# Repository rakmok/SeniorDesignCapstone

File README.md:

# SeniorDesignCapstone

This is the repository to record and motivate our capstone project for ECE 445: Senior Design in the Spring of 2025 titled PawFeast: Food on Demand. The group members are Arash Amiri, Kathryn Thompson, and Omkar Kulkarni.

The project entails the analysis, design, and build of a pet food dispensory system. If you wish to see each member's notebook, you can switch branches in github.com by clicking main or run git checkout \[member_first_name]-notebook. Each member hosts their own notebook on a different branch. The Hardware folder contains all of our KiCAD boards and other libraries. The images folder is only meant for displaying images to the README and the Assignments folder includes all of our important documents.

# Problem

All household pet owners must remember to feed their pets—whether they are birds, guinea pigs, rabbits, dogs, or cats—at set periods during the day. But there can be times when people forget to feed their pets, double feed them, or have trouble feeding them on schedule. This can be due to poor communication between family members or even occur when pet owners come home late from work or prior commitments. During these times, pets either overeat, go hungry, or eat irregularly. As a result, timer-based pet feeders have been developed to release food at set intervals. When food sits out for extended periods of time, the risk of the food becoming stale or getting infected with bugs increases drastically.

If an insect is near your food, it is a common reaction to remove or swat it away, but that mechanism is not present for the pet’s food bowl, especially when the family is not at home. Another issue is that smarter pets can nose into the food storage and overeat or eat something that their bodies will reject (like chocolate for dogs). With a set schedule to limit food dispensation throughout the day, the pet will not take advantage of either a careless overpour of food or of an unmanned food station. Furthermore, data on how much food was dispensed and eaten will help track and optimize the pet’s eating habits.

# Solution

We are seeking to solve this problem by having timers coupled with a button and RFID component to release food—thus preventing overeating. Given all of these conditions, the dispenser will release the pet food. This ensures that the pet is not only fed on time, but that the food is not polluted when the pet goes to eat; additionally, a chime will go off signaling to the pet that it is time for them to eat. We will incorporate a notification system to alert the owner(s) whether the pet has eaten or when the food store has low levels of food.

If the pet were to not eat all the food at once and leave the food dispenser, the pressure sensor will tell the dispenser to cover the food until the pet returns ensuring freshness and preventing bugs.

# Solution Components

## Subsystem 1: Refilling Food Store

The subsystem for checking if the food store is empty will include a through-beam optical sensor that is able to determine whether an object is present—this will serve to detect whether the food inside of the container is low and needs to be refilled. When the food store reaches a certain level, a signal will be sent to subsystem 6 (the brain), which will send an automated message to notify the owner to refill the food store.

## Subsystem 2: Power System

The power system will supply energy to all of the various subsystems, including the microcontroller of subsystem 6 (the brain), the stepper motor driver in subsystem 3, and the various sensors in subsystems 1 (refilling food) and 3 (food dispenser). The low voltage buses will be 3.3V, 12V, and 5V, all of which will be powered by a combination of rechargeable lithium-ion batteries with voltage regulators and buck converters. This compact, custom 3s2p battery pack will allow the pet dispenser to be portable, even for family vacations or road trips—more importantly, it will provide a steady current, even when the pack voltage drops (unlike standard AA/AAA cells). The 12V to 3.3V regulator chip will be Monolithic Power Systems’s MP2315SGJ-Z, which can take a 12V input and output up to 2.5A [4.7]. The 12V to 5V regulator chip will be Monolithic Power Systems’s MP2338GTL-Z [4.6]. The 12V input into the motor driver IC circuit will come straight from the battery pack. There will also be a backup supply voltage of 5V from a typical barrel jack wall-outlet, integrated into the brain board. This will implement the AMS1117 LDO, which is perfect for 5V to 3.3V power conversion. Just to be clear, this 5V barrel-jack addition will just be included on the brain board as a backup power subcircuit in case of power shutdown.

## Subsystem 3: Food Dispenser

This subsystem will utilize a E Series Nema 17 stepper motor that will rotate a door to the food container when needed and allow a set amount of food through before rotating again to close the door [4.8]. The motor will be controlled by a stepper motor controller IC (DRV8825) with a custom control circuit that takes in 12V and outputs 3.4V to the motor. We will define hard cut offs that will be coded for maximum amount of food to be dispensed and specify times at which food may be dispensed during the day.

The main objective of this subsystem is to make the system an on-demand food system. We will utilize a large button for the dog to step on when hungry. When pressed, the system will start the motors to release food, on the condition that enough time has elapsed since it ate last. The pet would be trained how to ask for food using this button. Only when the button is pressed and enough time has passed, will food then be dispensed.

## Subsystem 4: RFID for pet identification

We will have a receiver for a minimum of 2 HF RFID tags 9662 Long Distance Passive Alien H3. We will use the RC522 RFID chip for reading and writing to the RFID chips. The RFIDs would be used to signal which pet is using the dispenser, so the owner is able to utilize the same dispenser for one or more pets.

## Subsystem 5: User Interface

The subsystem for notifications will be a web application that we will build that is able to connect with the pet feed dispenser system. For the application side, we will utilize Bottle for our backend, SQLite for our database, and html pages for our frontend to create a user friendly method to check the pet’s eating habits. This will notify users for when the pet has been fed, if the food tank is low and requires refiling, and if the food was covered due to an empty bowl or a partially filled one.

## Subsystem 6: Brain

The brain subsystem will take in inputs from all of the other sensor subsystems and output the according signals to the user interface (for notifications) and the food dispenser motor driver. This system will also track the amount of time that has passed and sound a soft chime for when enough time has passed for the pet to be able to eat. The ESP32 WROOM-32E-4N microcontroller, known for its wifi connectivity and security measures, would have a set of I/O pins for taking in these signals. This MCU programmer circuit and other control level circuitry—firmware or equivalent—would be incorporated onto this board along with a UART circuit to detect pet RFIDs (done with the UHF RFID reader JRD-4035).

# High Level Requirements List

For this project to be considered successful, our project must meet the following requirements:

- The **Pet Food Dispenser** must **not** dispense food before user preset times, such as **10 AM and 6 PM, daily**, with a **10-minute tolerance**.
- The **Pet Food Dispenser** must dispense food into the **designated food bowl** upon detecting the **presence of the pet** via the **button** and the **2+ RFID tags** on the pet’s collar **within 2 minutes**.
- The **user interface** must update **within 5 minutes** of an event on the application we create, detailing:
  - The pet’s **feeding status**
  - **Low food store** notifications at **20% & 10%**
  - **Unfinished meals**

# Results

# Demo

Here is the link to our demonstration video:
[Demo](https://www.youtube.com/watch?v=mT6wlLyjihs) <br><br><br>

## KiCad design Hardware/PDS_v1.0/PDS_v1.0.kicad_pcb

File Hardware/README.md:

# KiCAD Board Repository

This is the hardware repository with all of our KiCAD boards. We have five: two power boards, a brain board, an RFID board, and the motor driver board. If you are unable to see symbols on the schematic capture, you will need to go to schematic editor->Preferences->Configure Paths and manually add a large parts library that you can link from Hardware/Libraries folder courtesey of Illini Solar Car.

For all of the parts that we dowloaded from 3rd party sites, there is a folder called Parts (Hardware/Parts), which has the symbols, footprints, and some .step files. This can be linked by going to schematic editor->Preferences->Manage Symbol Libraries. The same must be done for all the footprints in the PCB editor under Preferences->Manage Footprint Libraries. Three images below depict the path libraries for Omkar's KiCAD. Note that Omkar's file path for the Solar Car library is completely different and the Parts library is about three steps upstream from what you should link—you should add SeniorDesignCapstone/Hardware/Parts as your filepath instead of ../ECE445/Parts. There is also a courtesey template to get started, though you will need to set up the Illini Solar Car Libraries folder or you won't be able to retrieve parts with the 'a' hotkey.

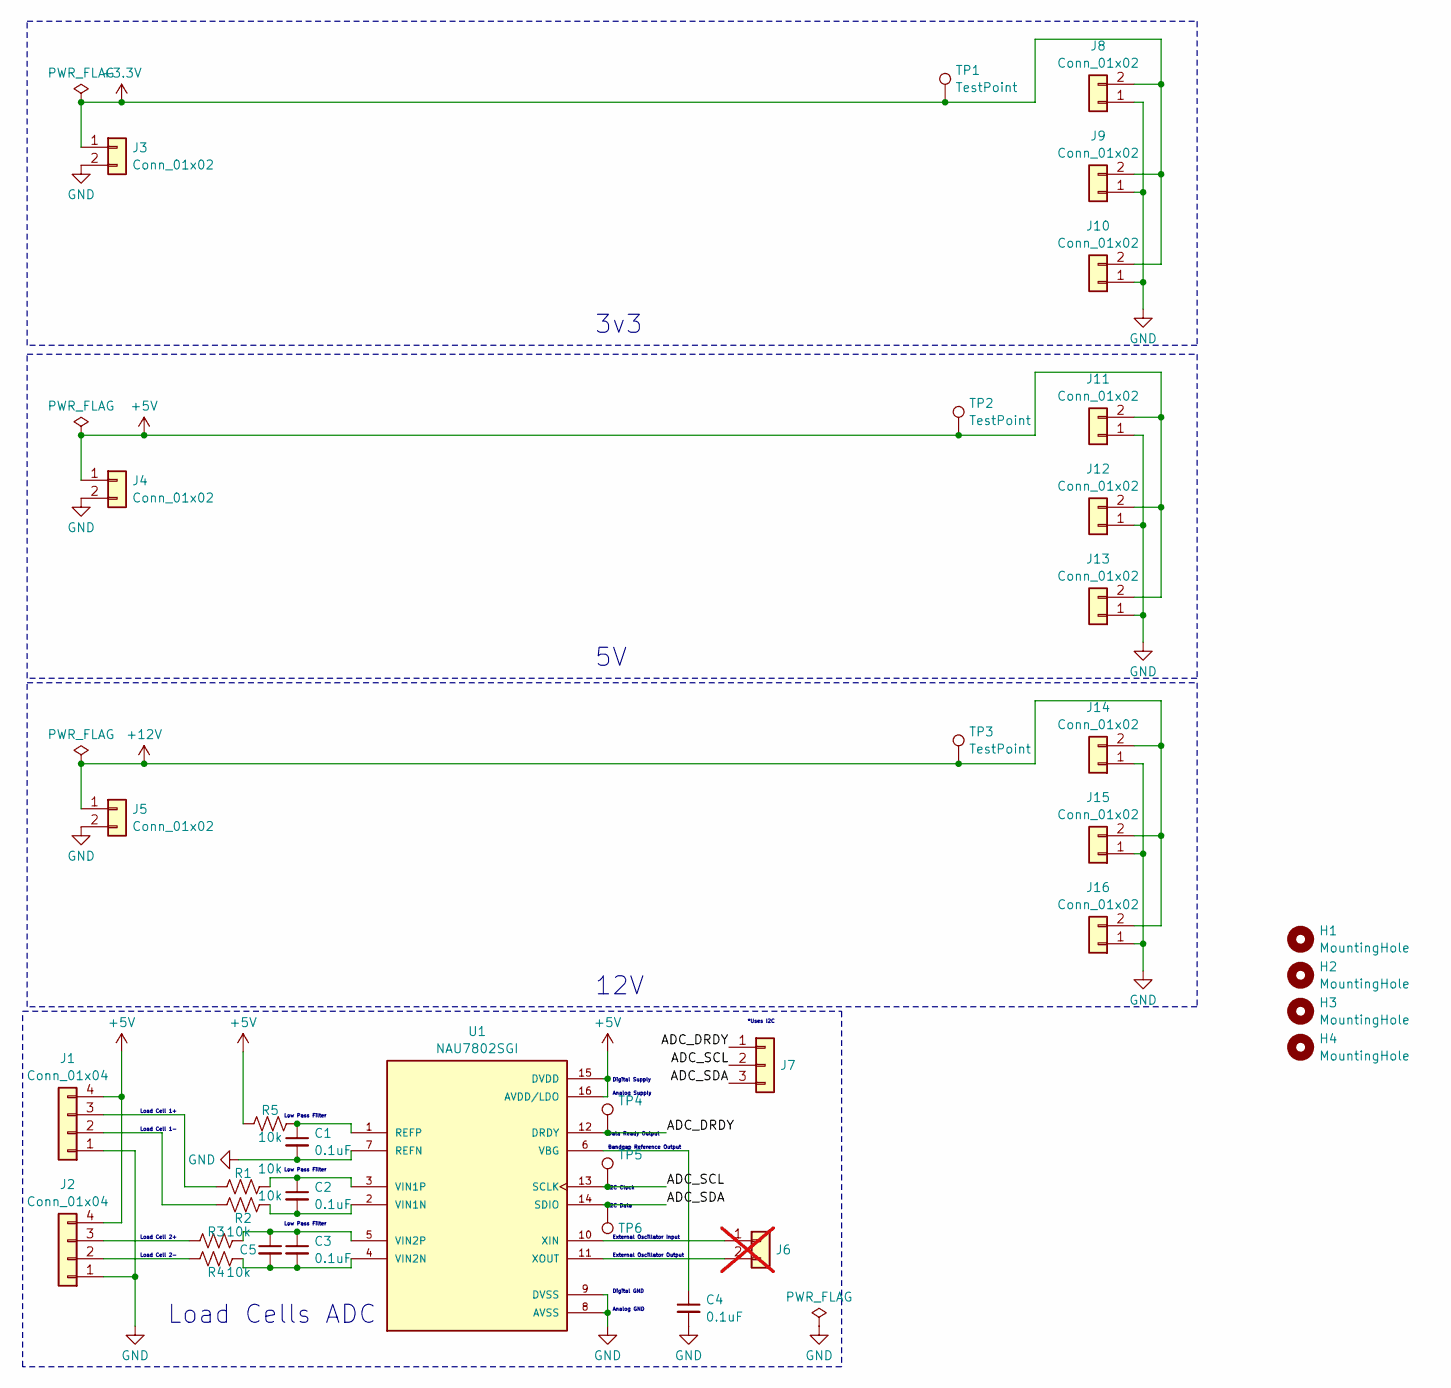
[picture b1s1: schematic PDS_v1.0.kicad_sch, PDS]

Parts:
C1, C2, C3, C4: 0.1uF; C_0805_2012Metric; MPN CC0603KRX7R7BB104
C5: 470uF; C_Radial_D10.0mm_H12.5mm_P5.00mm
H1, H2, H3, H4: MountingHole; MountingHole_3.2mm_M3; MPN NA
J1, J2: Conn_01x04; Molex_KK-254_AE-6410-04A_1x04_P2.54mm_Vertical; MPN 0022292041
J3, J4, J5, J8, J9, J10, J11, J12, J13, J14, J15, J16: Conn_01x02; Molex_KK-254_AE-6410-02A_1x02_P2.54mm_Vertical
J6: Conn_01x02; Molex_KK-254_AE-6410-02A_1x02_P2.54mm_Vertical; not fitted
J7: Conn_01x03; Molex_KK-254_AE-6410-03A_1x03_P2.54mm_Vertical
R1, R2, R3, R4, R5: 10k; R_0805_2012Metric; MPN HRG3216P-1002-B-T1
TP1, TP2, TP3, TP4, TP5, TP6: TestPoint; TestPoint_Keystone_5010-5014_Multipurpose
U1: NAU7802SGI; SOIC127P600X175-16N; PARTREV 2.6

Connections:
+3V3: J3.1, J8.2, J9.2, J10.2, TP1.1
+5V: J1.4, J2.4, J4.1, J11.2, J12.2, J13.2, R5.1, TP2.1, U1.15 (DVDD), U1.16 (AVDD/LDO)
+12V: J5.1, J14.2, J15.2, J16.2, TP3.1
/ADC_DRDY: J7.1, TP4.1, U1.12 (DRDY)
/ADC_SCL: J7.2, TP5.1, U1.13 (SCLK)
/ADC_SDA: J7.3, TP6.1, U1.14 (SDIO)
GND: C1.2, C4.2, J1.1, J2.1, J3.2, J4.2, J5.2, J8.1, J9.1, J10.1, J11.1, J12.1, J13.1, J14.1, J15.1, J16.1, U1.7 (REFN), U1.8 (AVSS), U1.9 (DVSS)
unnamed: J1.2, R2.1
unnamed: J1.3, R1.1
unnamed: J2.2, R4.1
unnamed: J2.3, R3.1
unnamed: J6.1, U1.10 (XIN)
unnamed: J6.2, U1.11 (XOUT)
unnamed: C1.1, R5.2, U1.1 (REFP)
unnamed: C4.1, U1.6 (VBG)
unnamed: C2.2, R2.2, U1.2 (VIN1N)
unnamed: C2.1, R1.2, U1.3 (VIN1P)
unnamed: C3.2, C5.2, R4.2, U1.4 (VIN2N)
unnamed: C3.1, C5.1, R3.2, U1.5 (VIN2P)

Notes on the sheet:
Load Cell 2-
Low Pass Filter
Analog GND
3v3
Load Cell 2+
Load Cell 1+
12V
Analog Supply
Digital Supply
*Uses I2C
Load Cells ADC
Bandgap Reference Output
External Oscillator Input
Data Ready Output
Digital GND
I2C Data
External Oscillator Output
Load Cell 1-
I2C Clock

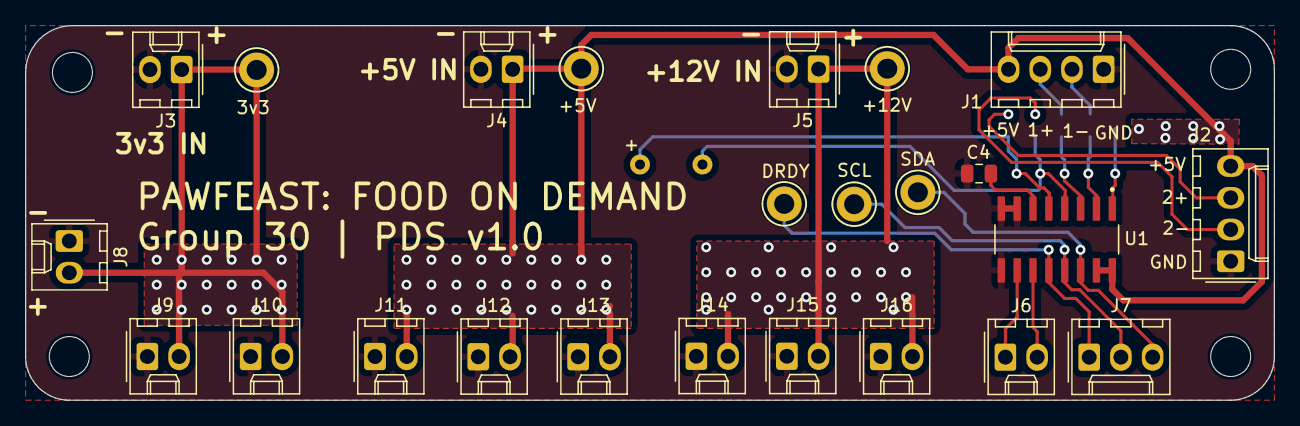
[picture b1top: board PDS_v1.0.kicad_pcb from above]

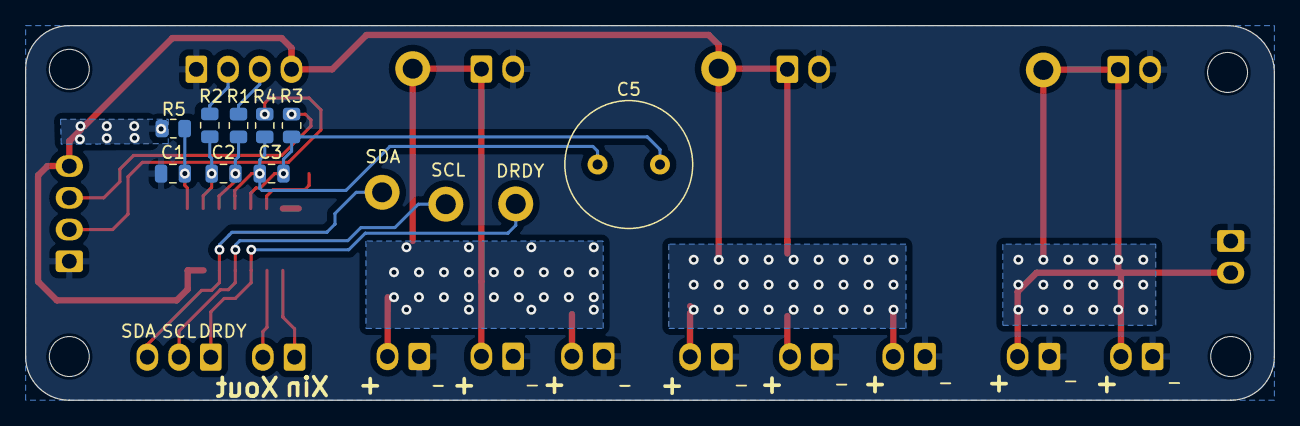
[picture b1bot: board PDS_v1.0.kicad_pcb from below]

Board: 2 copper layers, 100.0 x 30.0 mm, 37 parts (9 on the bottom side), 19 nets.

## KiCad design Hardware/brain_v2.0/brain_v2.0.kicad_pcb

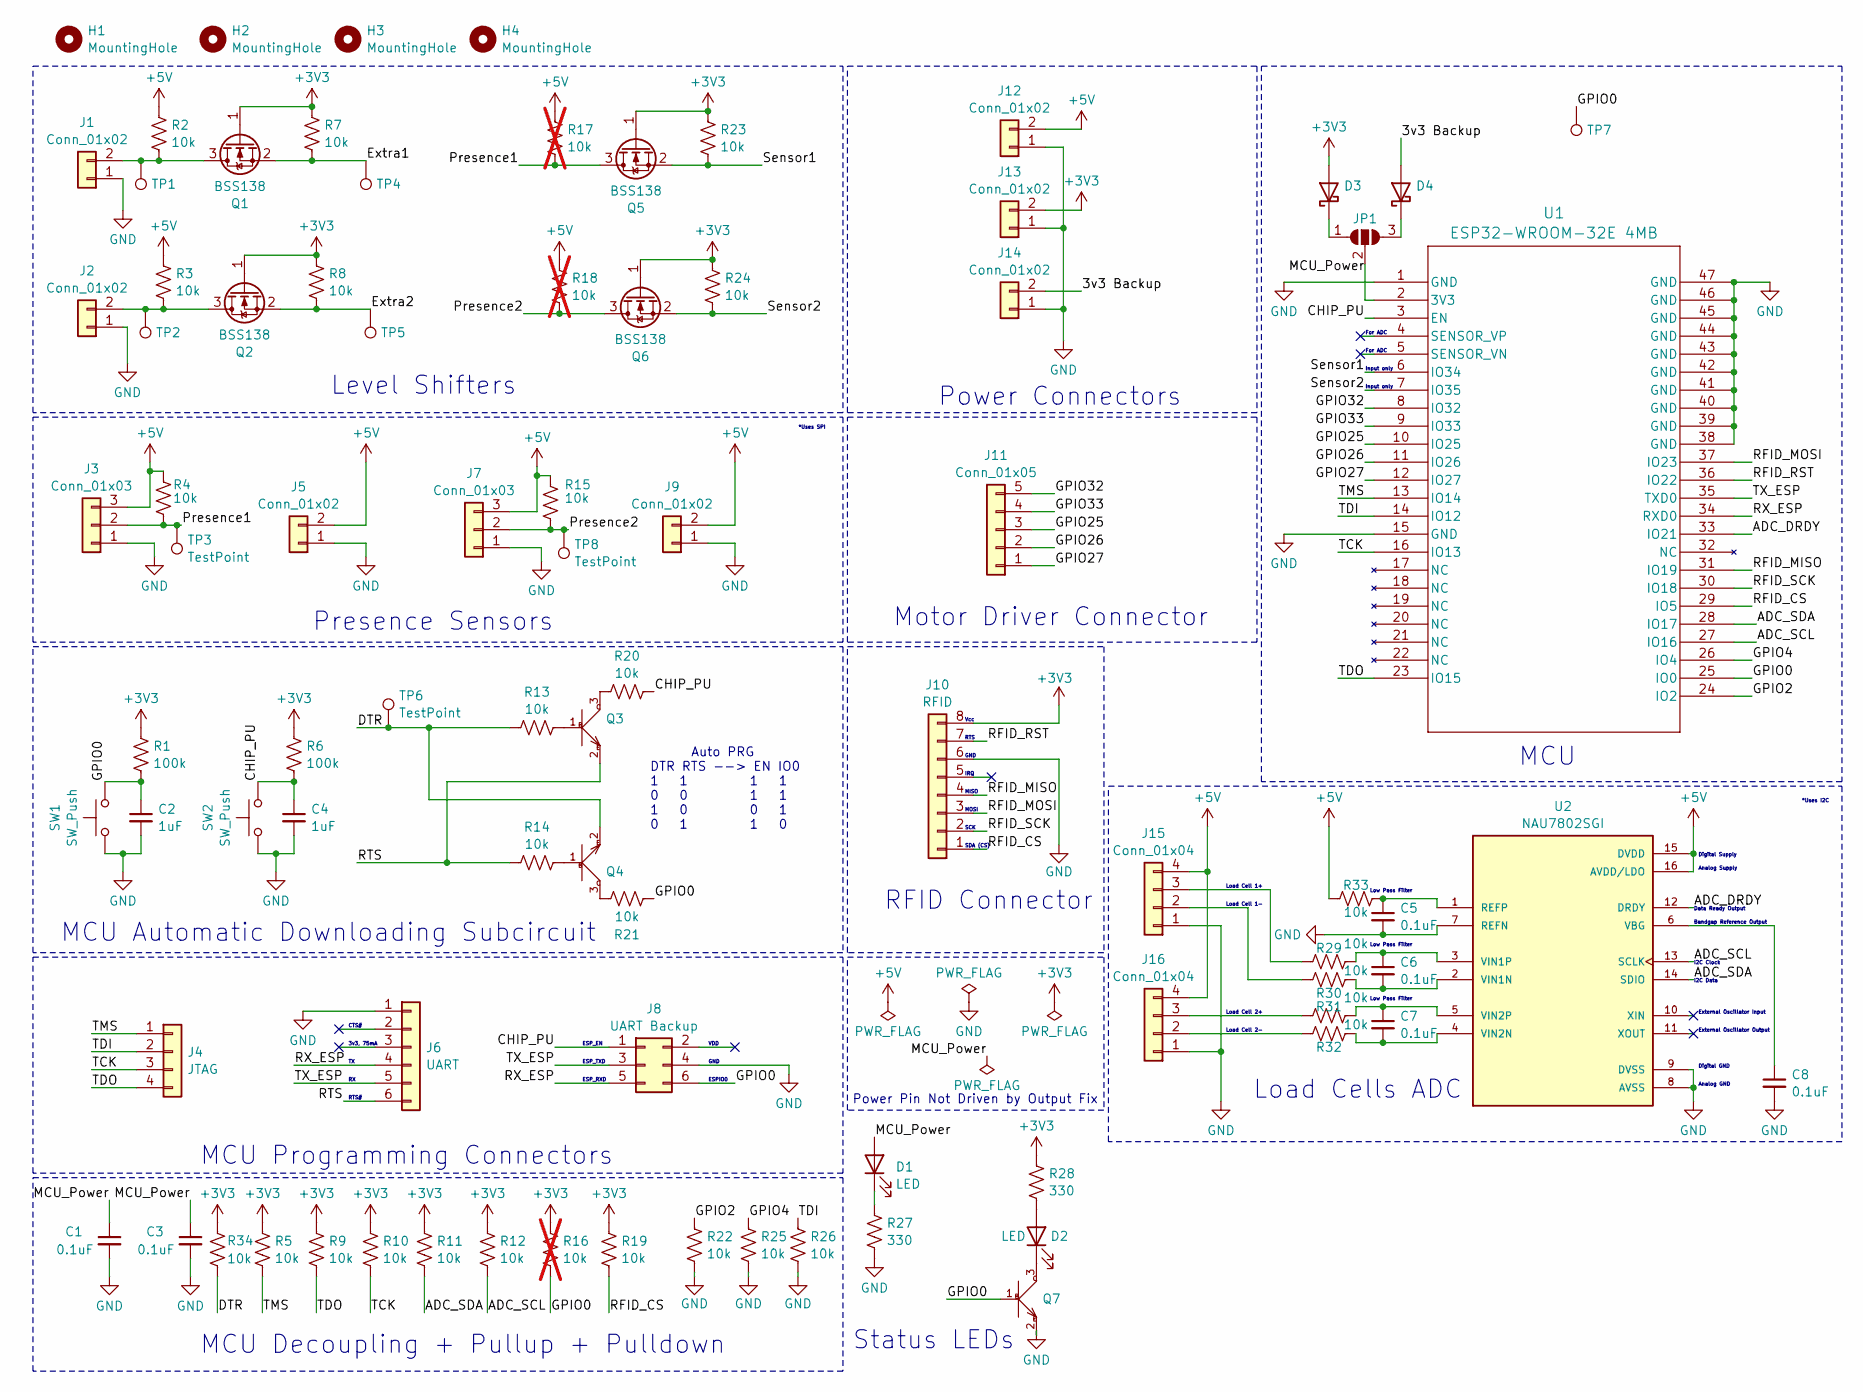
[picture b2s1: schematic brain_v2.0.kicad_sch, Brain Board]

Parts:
C1, C3: 0.1uF; C_0603_1608Metric; MPN C0603C103F3GECAUTO
C2, C4: 1uF; R_0603_1608Metric; MPN TMK107B7105KA-T
C5, C6, C7, C8: 0.1uF; C_0603_1608Metric; MPN CC0603KRX7R7BB104
D1: LED; LED_0603_1608Metric; MPN LTST-C191KFKT
D2: LED; LED_0603_1608Metric; MPN LTST-C190GKT
D3, D4: D_Schottky; VS_30BQ015_M3_9AT; MPN VS-30BQ015-M3/9AT
H1, H2, H3, H4: MountingHole; MountingHole_3.2mm_M3; MPN NA
J1, J2, J5, J9, J12, J13, J14: Conn_01x02; Molex_KK-254_AE-6410-02A_1x02_P2.54mm_Vertical; MPN 1718560102
J3, J7: Conn_01x03; Molex_KK-254_AE-6410-03A_1x03_P2.54mm_Vertical; MPN 0022272031
J4: JTAG; PinSocket_1x04_P2.54mm_Vertical; MPN M20-9990446
J6: UART; PinHeader_1x06_P2.54mm_Vertical; MPN M20-9990645
J8: UART Backup; 61200621621; MPN 61200621621
J10: RFID; Harting_har-flexicon_14110813001xxx_1x08-MP_P2.54mm_Vertical; MPN 14110813001000
J11: Conn_01x05; PinHeader_1x05_P2.54mm_Vertical; MPN M20-9990546
J15, J16: Conn_01x04; Molex_KK-254_AE-6410-04A_1x04_P2.54mm_Vertical; MPN 0022292041
JP1: SolderJumper_3_Open; SolderJumper-3_P1.3mm_Open_RoundedPad1.0x1.5mm; MPN NA
Q1, Q2, Q5, Q6: BSS138; SOT-23; MPN BSS138
Q3, Q4, Q7: SMD-TRANSISTORS-NPN-25V-500MW_SOT-23_; S8050-SMD; MPN S8050; DigiKey_Part_Number 3372-S8050TR-ND
R1, R6: 100k; R_0805_2012Metric; MPN RC0805FR-07100KL
R2, R3, R4, R5, R7, R8, R9, R10, R11, R12, R13, R14, R15, R19, R20, R21, R22, R23, R24, R25, R26, R29, R30, R31, R32, R33, R34: 10k; R_1206_3216Metric; MPN HRG3216P-1002-B-T1
R16, R17, R18: 10k; R_1206_3216Metric; MPN HRG3216P-1002-B-T1; not fitted
R27, R28: 330; R_0603_1608Metric
SW1, SW2: SW_Push; SW_SPST_B3U-1000P; MPN B3U-1000P
TP1, TP2, TP3, TP4, TP5, TP6, TP7, TP8: TestPoint; TestPoint_Keystone_5010-5014_Multipurpose; MPN 36-5011-ND
U1: ESP32-WROOM-32E 4MB; ESP32-WROOM-32E-N4; MPN ESP32-WROOM-32E-N4
U2: NAU7802SGI; SOIC127P600X175-16N; PARTREV 2.6

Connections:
+3V3: D3.2 (A), J10.8, J13.2, Q1.1 (G), Q2.1 (G), Q5.1 (G), Q6.1 (G), R1.1, R5.1, R6.1, R7.1, R8.1, R9.1, R10.1, R11.1, R12.1, R16.1, R19.1, R23.1, R24.1, R28.1, R34.1
+5V: J3.3, J5.2, J7.3, J9.2, J12.2, J15.4, J16.4, R2.1, R3.1, R4.1, R15.1, R17.1, R18.1, R33.1, U2.15 (DVDD), U2.16 (AVDD/LDO)
/3v3 Backup: D4.2 (A), J14.2
/ADC_DRDY: U1.33 (IO21), U2.12 (DRDY)
/ADC_SCL: R12.2, U1.27 (IO16), U2.13 (SCLK)
/ADC_SDA: R11.2, U1.28 (IO17), U2.14 (SDIO)
/CHIP_PU: C4.1, J8.1, R6.2, R20.2, SW2.2, U1.3 (EN)
/DTR: Q4.2, R13.1, R34.2, TP6.1
/Extra1: Q1.2 (S), R7.2, TP4.1
/Extra2: Q2.2 (S), R8.2, TP5.1
/GPIO0: C2.1, J8.6, Q7.1, R1.2, R16.2, R21.2, SW1.2, TP7.1, U1.25 (IO0)
/GPIO2: R22.1, U1.24 (IO2)
/GPIO4: R25.1, U1.26 (IO4)
/GPIO25: J11.3, U1.10 (IO25)
/GPIO26: J11.2, U1.11 (IO26)
/GPIO27: J11.1, U1.12 (IO27)
/GPIO32: J11.5, U1.8 (IO32)
/GPIO33: J11.4, U1.9 (IO33)
/MCU_Power: C1.1, C3.1, D1.2 (A), JP1.2 (C), U1.2 (3V3)
/Presence1: J3.2, Q5.3 (D), R4.2, R17.2, TP3.1
/Presence2: J7.2, Q6.3 (D), R15.2, R18.2, TP8.1
/RFID_CS: J10.1, R19.2, U1.29 (IO5)
/RFID_MISO: J10.4, U1.31 (IO19)
/RFID_MOSI: J10.3, U1.37 (IO23)
/RFID_RST: J10.7, U1.36 (IO22)
/RFID_SCK: J10.2, U1.30 (IO18)
/RTS: J6.6, Q3.2, R14.1
/RX_ESP: J6.4, J8.5, U1.34 (RXD0)
/Sensor1: Q5.2 (S), R23.2, U1.6 (IO34)
/Sensor2: Q6.2 (S), R24.2, U1.7 (IO35)
/TCK: J4.3, R10.2, U1.16 (IO13)
/TDI: J4.2, R26.1, U1.14 (IO12)
/TDO: J4.4, R9.2, U1.23 (IO15)
/TMS: J4.1, R5.2, U1.13 (IO14)
/TX_ESP: J6.5, J8.3, U1.35 (TXD0)
GND: C1.2, C2.2, C3.2, C4.2, C5.2, C8.2, J1.1, J2.1, J3.1, J5.1, J6.1, J7.1, J8.4, J9.1, J10.6, J12.1, J13.1, J14.1, J15.1, J16.1, Q7.2, R22.2, R25.2, R26.2, R27.2, SW1.1, SW2.1, U1.1 (GND), U1.15 (GND), U1.38 (GND), U1.39 (GND), U1.40 (GND), U1.41 (GND), U1.42 (GND), U1.43 (GND), U1.44 (GND), U1.45 (GND), U1.46 (GND), U1.47 (GND), U2.7 (REFN), U2.8 (AVSS), U2.9 (DVSS)
unnamed: D1.1 (K), R27.1
unnamed: D2.2 (A), R28.2
unnamed: D2.1 (K), Q7.3
unnamed: D3.1 (K), JP1.1 (A)
unnamed: D4.1 (K), JP1.3 (B)
unnamed: J1.2, Q1.3 (D), R2.2, TP1.1
unnamed: J2.2, Q2.3 (D), R3.2, TP2.1
unnamed: J15.2, R30.1
unnamed: J15.3, R29.1
unnamed: J16.2, R32.1
unnamed: J16.3, R31.1
unnamed: Q3.1, R13.2
unnamed: Q3.3, R20.1
unnamed: Q4.1, R14.2
unnamed: Q4.3, R21.1
unnamed: C5.1, R33.2, U2.1 (REFP)
unnamed: C8.1, U2.6 (VBG)
unnamed: C6.2, R30.2, U2.2 (VIN1N)
unnamed: C6.1, R29.2, U2.3 (VIN1P)
unnamed: C7.2, R32.2, U2.4 (VIN2N)
unnamed: C7.1, R31.2, U2.5 (VIN2P)

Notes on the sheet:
Load Cell 1-
Low Pass Filter
Digital Supply
Load Cells ADC
Power Pin Not Driven by Output Fix
For ADC
RFID Connector
Load Cell 2-
ESPIO0
Auto PRG DTR RTS --> EN IO0 1 1 1 1 0 0 1 1 1 0 0 1 0 1 1 0
IRQ
ESP_TXD
I2C Data
MCU
Analog Supply
Digital GND
SCK
RTS
Load Cell 2+
CTS#
RTS#
VDD
Load Cell 1+
MCU Decoupling + Pullup + Pulldown
GND
MOSI
MCU Programming Connectors
MISO
External Oscillator Output
*Uses I2C
ESP_EN
MCU Automatic Downloading Subcircuit
Status LEDs
Input only
Power Connectors
Presence Sensors
Bandgap Reference Output
*Uses SPI
Level Shifters
Motor Driver Connector

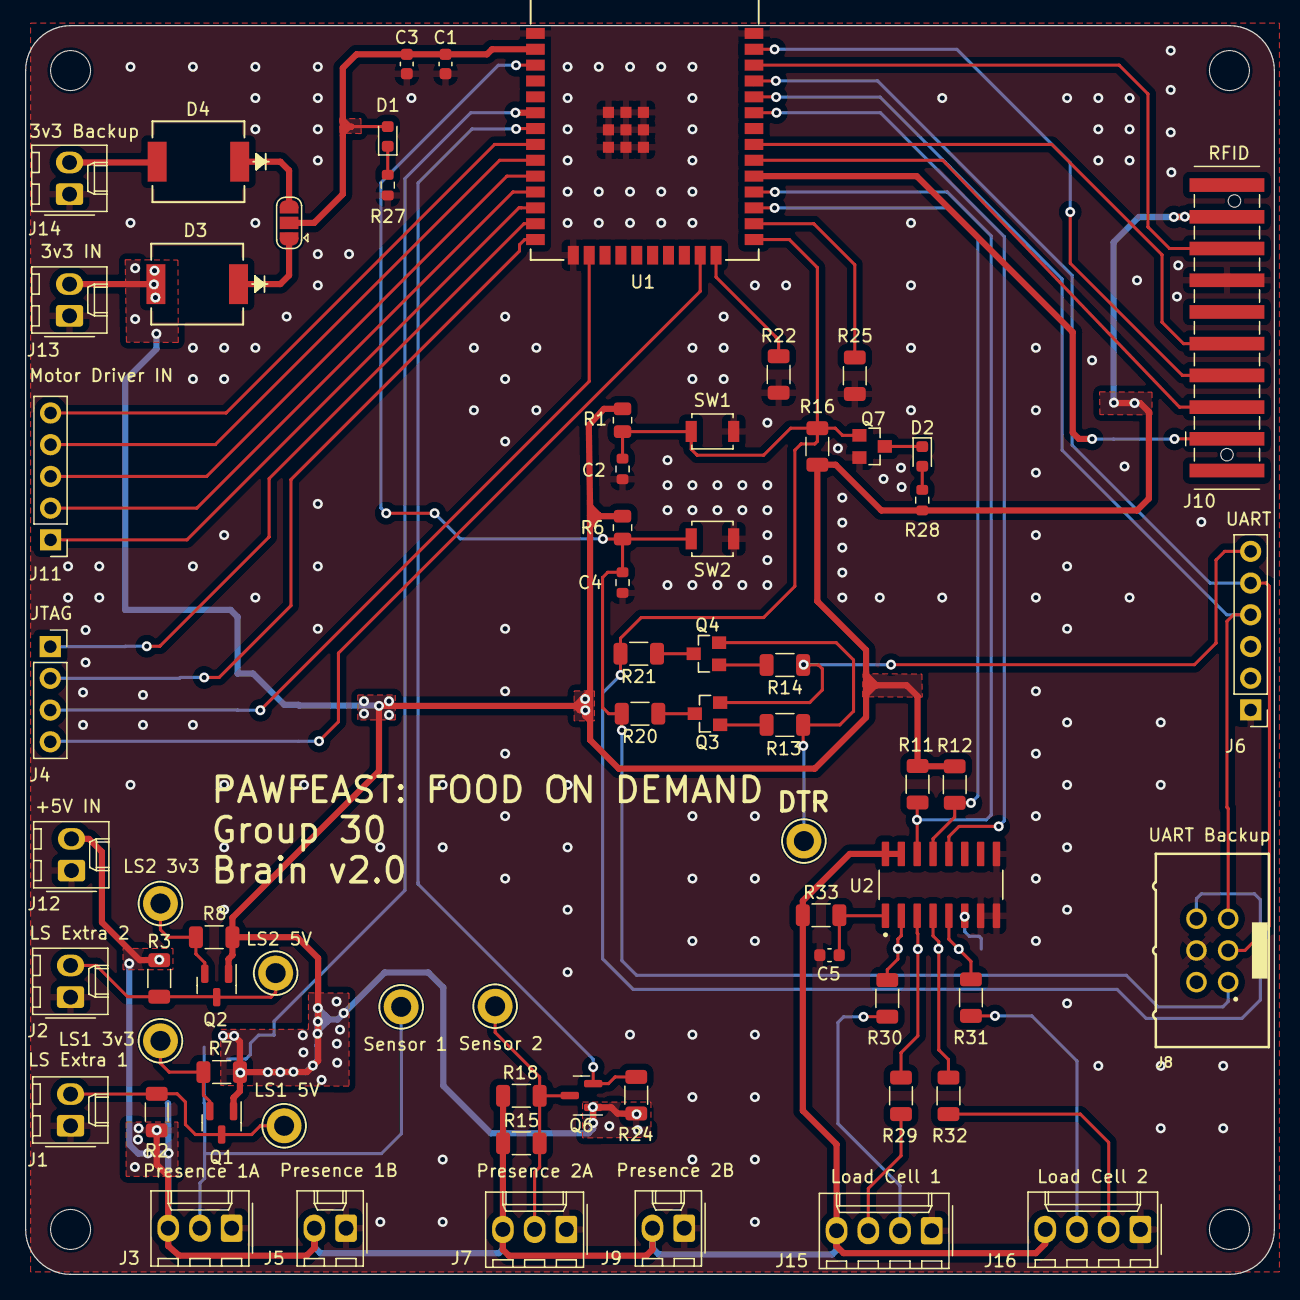
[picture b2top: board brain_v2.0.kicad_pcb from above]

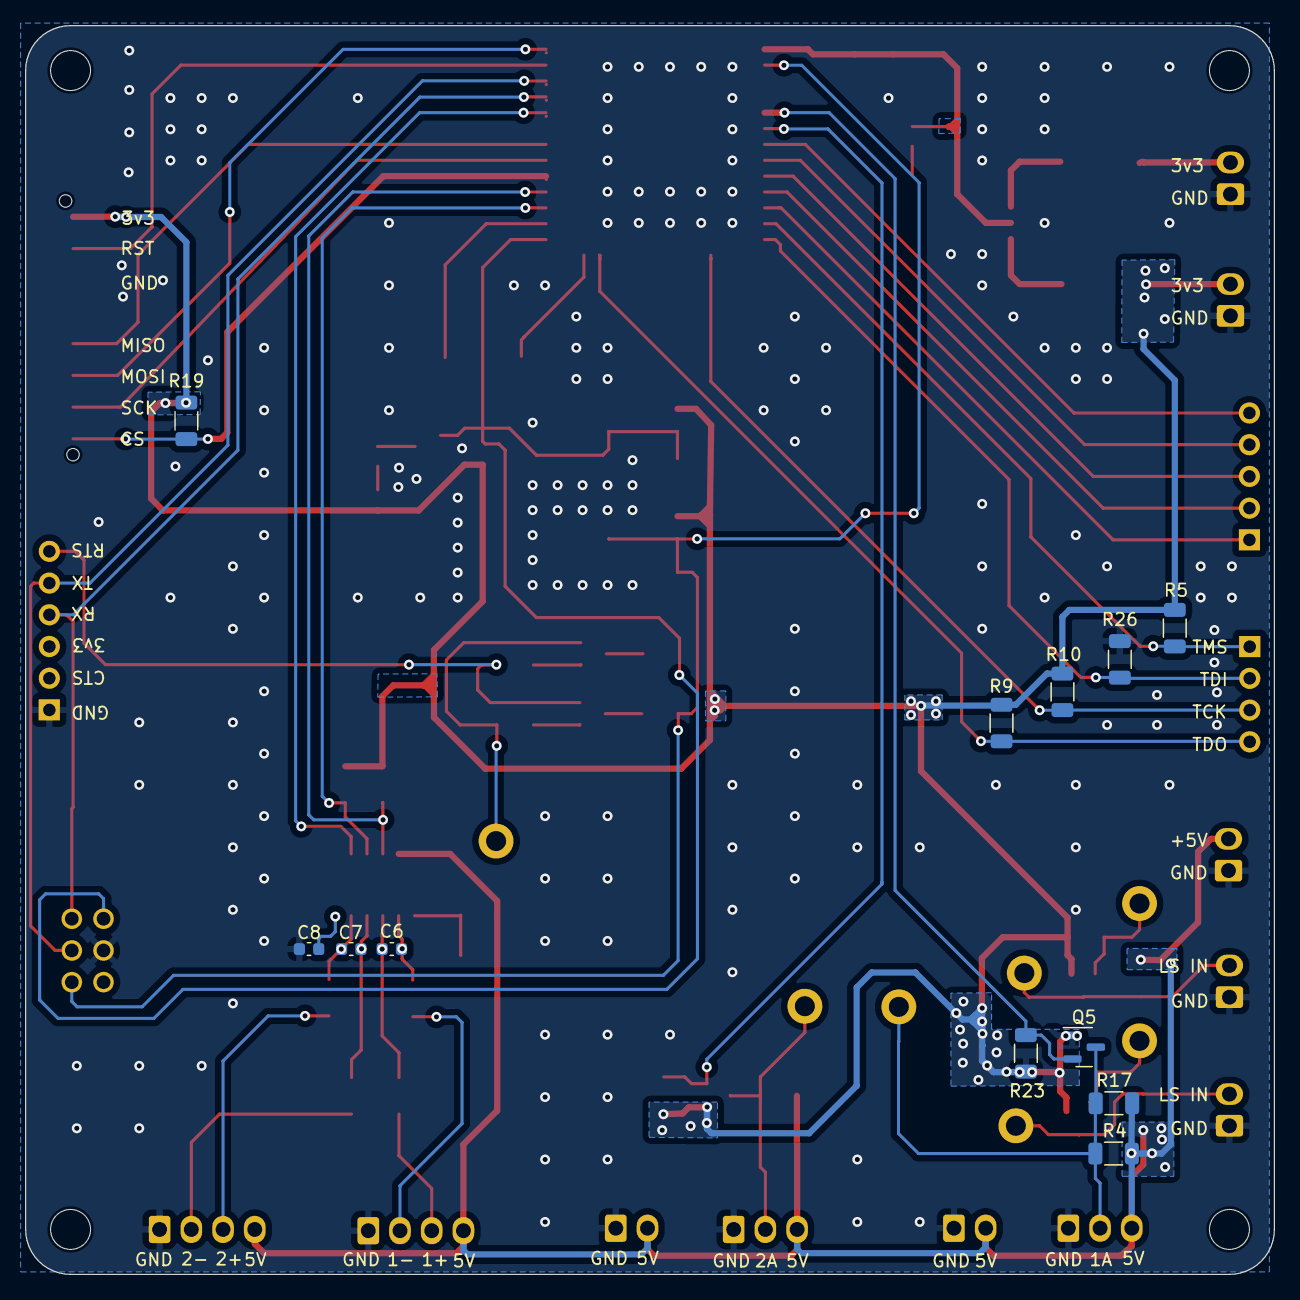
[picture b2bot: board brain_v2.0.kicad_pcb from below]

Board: 2 copper layers, 100.0 x 100.0 mm, 84 parts (12 on the bottom side), 57 nets.

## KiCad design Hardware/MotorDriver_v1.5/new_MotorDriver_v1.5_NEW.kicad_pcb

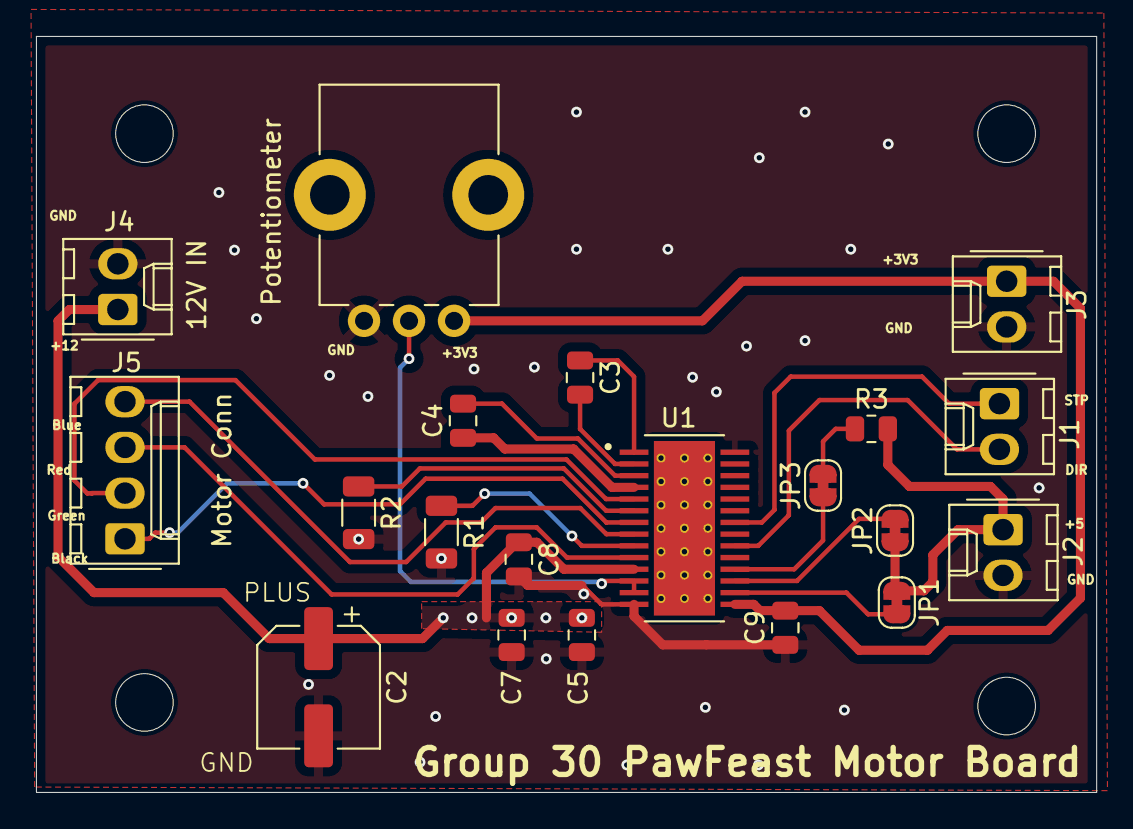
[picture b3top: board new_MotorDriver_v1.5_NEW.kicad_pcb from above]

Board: 2 copper layers, 58.9 x 42.0 mm, 24 parts (0 on the bottom side), 20 nets.

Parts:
12V IN: 12V Pwr; Molex_KK-254_AE-6410-02A_1x02_P2.54mm_Vertical
C2: 100uF; CP_Elec_6.3x5.8
C3: 10uF; C_0805_2012Metric
C4, C7, C8: 0.1uF; C_0805_2012Metric
C5: 4.7uF; C_0805_2012Metric
C9: 0.47uF; C_0805_2012Metric
H1, H2, H3, H4: MountingHole; MountingHole_3.2mm_M3
J1, J2, J3: Conn_01x02; Molex_KK-254_AE-6410-02A_1x02_P2.54mm_Vertical
JP1, JP2, JP3: SolderJumper_2_Bridged; SolderJumper-2_P1.3mm_Bridged_RoundedPad1.0x1.5mm
Motor Conn: J5; Molex_KK-254_AE-6410-04A_1x04_P2.54mm_Vertical
Potentiometer: 10k; Potentiometer_Bourns_PTV09A-1_Single_Vertical
R1, R2: 0.10; R_1206_3216Metric
R3: 10k; R_0805_2012Metric
U1: DRV8825PWPR; IC_TPS61196PWPRQ1

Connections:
+3V3: C9.2, J3.1, Potentiometer.1, U1.15 (V3P3OUT)
+5V: J2.1, JP1.1 (A), JP2.1 (A), R3.2
+12V: 12V IN.1, C2.1, C4.1, C5.1, C7.1, C8.1, U1.4 (VMA), U1.11 (VMB)
/DIR: J1.2, U1.20 (DIR)
/STP: J1.1, U1.22 (STEP)
GND: 12V IN.2, C2.2, C5.2, C7.2, C8.2, C9.1, J2.2, J3.2, Potentiometer.3, R1.2, R2.2, U1.14 (GND), U1.28 (GND)
unnamed: Motor Conn.1, U1.7 (AOUT2)
unnamed: Motor Conn.2, U1.5 (AOUT1)
unnamed: Motor Conn.3, U1.10 (BOUT1)
unnamed: Motor Conn.4, U1.8 (BOUT2)
unnamed: JP1.2 (B), U1.16 (~NRESET)
unnamed: JP2.2 (B), U1.17 (NSLEEP)
unnamed: JP3.1 (A), U1.18 (NFAULT)
unnamed: JP3.2 (B), R3.1
unnamed: Potentiometer.2, U1.12 (AVREF), U1.13 (BVREF)
unnamed: C3.1, U1.1 (CP1)
unnamed: C3.2, U1.2 (CP2)
unnamed: R2.1, U1.6 (ISENA)
unnamed: R1.1, U1.9 (ISENB)
unnamed: C4.2, U1.3 (VCP)

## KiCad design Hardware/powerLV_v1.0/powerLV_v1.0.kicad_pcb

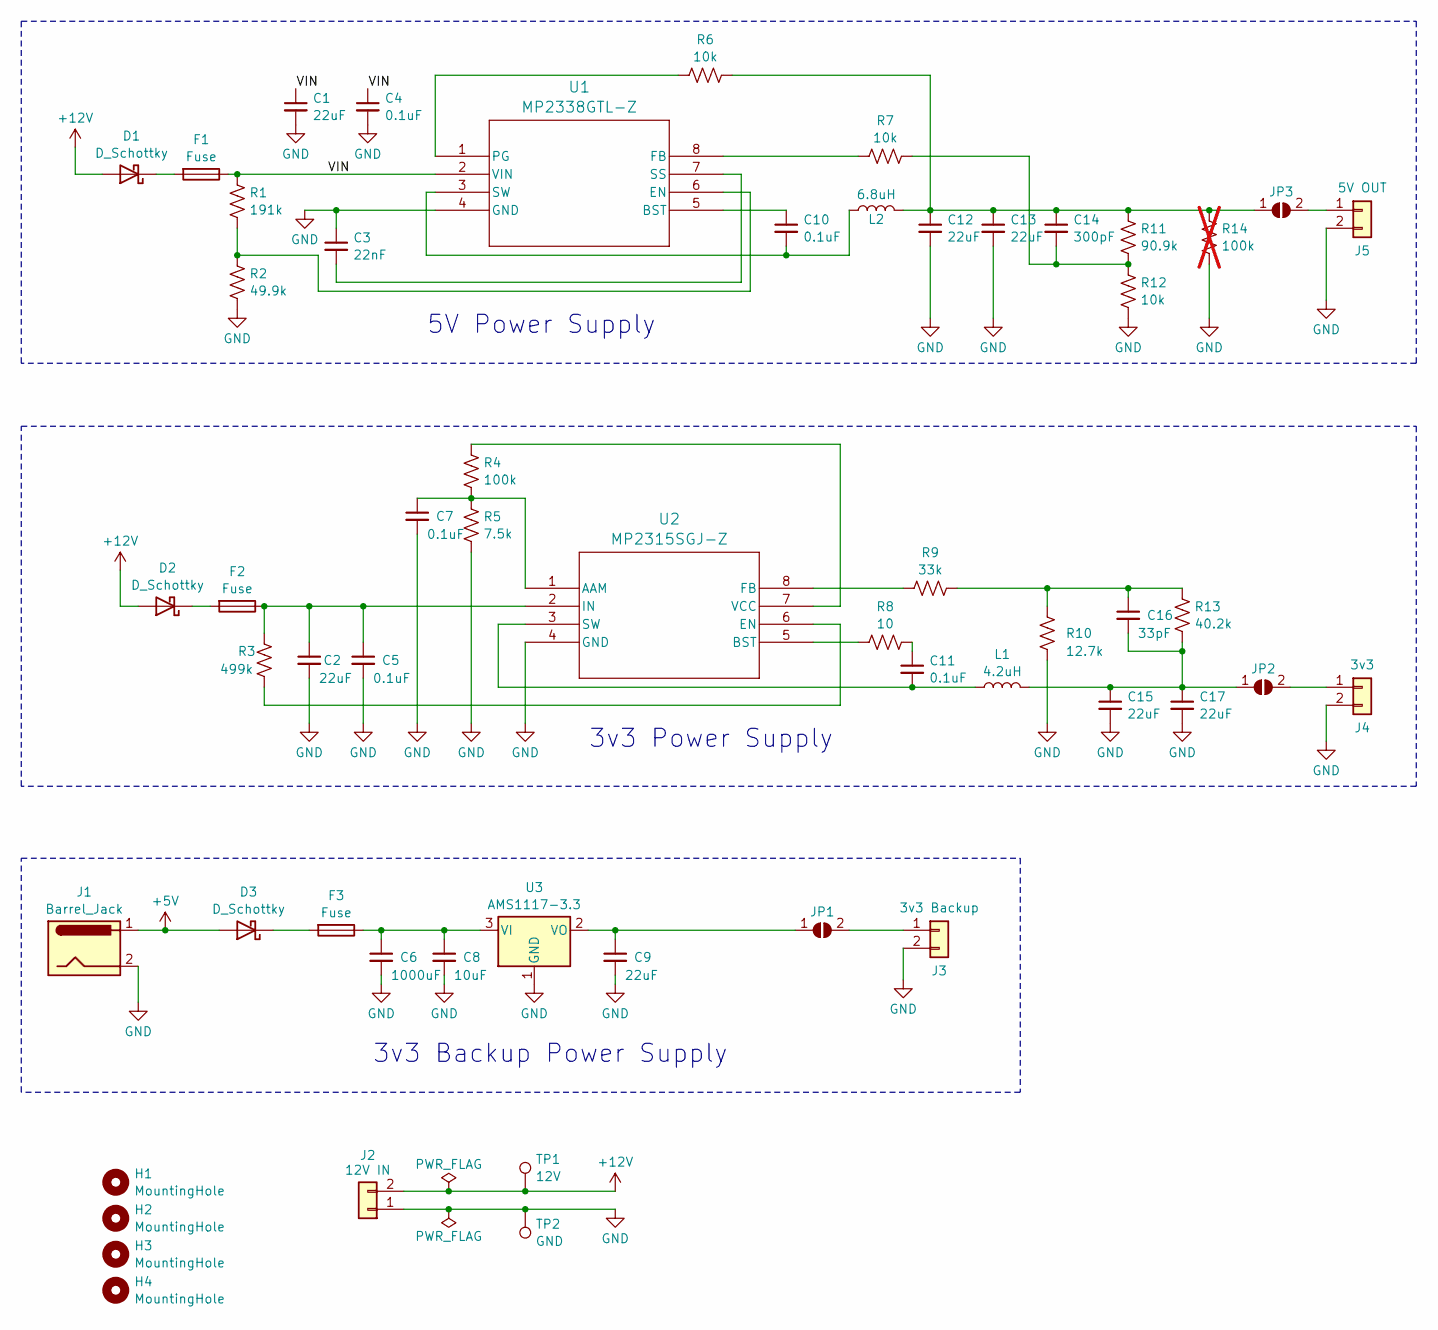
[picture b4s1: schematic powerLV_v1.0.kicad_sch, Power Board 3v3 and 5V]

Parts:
C1, C2, C9, C12, C13, C15, C17: 22uF; C_0805_2012Metric; MPN CL21A226MAYNNNE
C3: 22nF; C_0805_2012Metric; MPN C0805C223F3GECAUTO
C4, C5, C7, C10, C11: 0.1uF; C_0603_1608Metric; MPN C0603C103F3GECAUTO
C6: 1000uF; CAP_PC_10X12P7_NCH; MPN PCG1A102MCL1GS
C8: 10uF; R_1206_3216Metric; MPN F951E106KAAAQ2
C14: 300pF; C_0805_2012Metric; MPN 08053C301JAT2A
C16: 33pF; R_0402_1005Metric; MPN GJM1555C1H330FB01D
D1, D2, D3: D_Schottky; VS_30BQ015_M3_9AT; MPN VS-30BQ015-M3/9AT
F1, F2, F3: Fuse; FUSE_4628; MPN 36-4628-ND
H1, H2, H3, H4: MountingHole; MountingHole_3.2mm_M3; MPN NA
J1: Barrel_Jack; BarrelJack_CUI_PJ-102AH_Horizontal; MPN PJ-102AH
J2: 12V IN; Molex_KK-254_AE-6410-02A_1x02_P2.54mm_Vertical; MPN 1718560102
J3: 3v3 Backup; Molex_KK-254_AE-6410-02A_1x02_P2.54mm_Vertical; MPN 1718560102
J4: 3v3; Molex_KK-254_AE-6410-02A_1x02_P2.54mm_Vertical; MPN 1718560102
J5: 5V OUT; Molex_KK-254_AE-6410-02A_1x02_P2.54mm_Vertical; MPN 1718560102
JP1, JP2, JP3: SolderJumper_2_Open; SolderJumper-2_P1.3mm_Open_RoundedPad1.0x1.5mm; MPN NA
L1: 4.2uH; WE-TPC_5828; MPN 744053004
L2: 6.8uH; WE-PD_6050R; MPN 7447786006
R1: 191k; R_1210_3225Metric; MPN ERJ-14NF1913U
R2: 49.9k; R_2512_6332Metric; MPN RMCF2512FT49K9
R3: 499k; R_0805_2012Metric; MPN RCS0805499KFKEA
R4: 100k; R_0805_2012Metric; MPN RC0805FR-07100KL
R5: 7.5k; R_0805_2012Metric; MPN CRCW08057K50FKEAHP
R6, R7, R12: 10k; R_1206_3216Metric; MPN HRG3216P-1002-B-T1
R8: 10; R_2512_6332Metric; MPN CRGP2512F10R
R9: 33k; R_0805_2012Metric; MPN RCS080533K0FKEA
R10: 12.7k; R_1210_3225Metric; MPN CRCW121012K7FKEA
R11: 90.9k; R_1206_3216Metric; MPN RNCP1206FTD90K9
R13: 40.2k; R_0805_2012Metric; MPN CRCW080540K2FKEAHP
R14: 100k; R_0805_2012Metric; MPN RC0805FR-07100KL; not fitted
TP1: 12V; TestPoint_Keystone_5010-5014_Multipurpose; MPN 36-5010-ND
TP2: GND; TestPoint_Keystone_5010-5014_Multipurpose; MPN 36-5011-ND
U1: MP2338GTL-Z; SOT583_MP2338_MNP; MPN MP2338GTL-Z
U2: MP2315SGJ-Z; TSOT23-8_MP2315S_MNP; MPN MP2315SGJ-Z
U3: AMS1117-3.3; SOT-223-3_TabPin2; MPN AMS1117-3.3

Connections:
+5V: D3.2 (A), J1.1
+12V: D1.2 (A), D2.2 (A), J2.2, TP1.1
/VIN: C1.1, C4.1, F1.1, R1.1, U1.2 (VIN)
unnamed: C11.1, R8.2
unnamed: C14.2, R7.2, R11.2, R12.1
unnamed: C16.1, R9.2, R10.1, R13.2
unnamed: D1.1 (K), F1.2
unnamed: D2.1 (K), F2.2
unnamed: D3.1 (K), F3.2
unnamed: J3.1, JP1.2 (B)
unnamed: J4.1, JP2.2 (B)
unnamed: J5.1, JP3.2 (B)
unnamed: C9.1, JP1.1 (A), U3.2 (VO)
unnamed: C15.1, C16.2, C17.1, JP2.1 (A), L1.2, R13.1
unnamed: C12.1, C13.1, C14.1, JP3.1 (A), L2.2, R6.2, R11.1, R14.1
unnamed: C10.1, U1.5 (BST)
unnamed: R1.2, R2.1, U1.6 (EN)
unnamed: R7.1, U1.8 (FB)
unnamed: R6.1, U1.1 (PG)
unnamed: C3.2, U1.7 (SS)
unnamed: C10.2, L2.1, U1.3 (SW)
unnamed: C7.1, R4.2, R5.1, U2.1 (AAM)
unnamed: R8.1, U2.5 (BST)
unnamed: R3.2, U2.6 (EN)
unnamed: R9.1, U2.8 (FB)
unnamed: C2.1, C5.1, F2.1, R3.1, U2.2 (IN)
unnamed: C11.2, L1.1, U2.3 (SW)
unnamed: R4.1, U2.7 (VCC)
unnamed: C6.1, C8.1, F3.1, U3.3 (VI)

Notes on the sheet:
5V Power Supply
3v3 Backup Power Supply
3v3 Power Supply

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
